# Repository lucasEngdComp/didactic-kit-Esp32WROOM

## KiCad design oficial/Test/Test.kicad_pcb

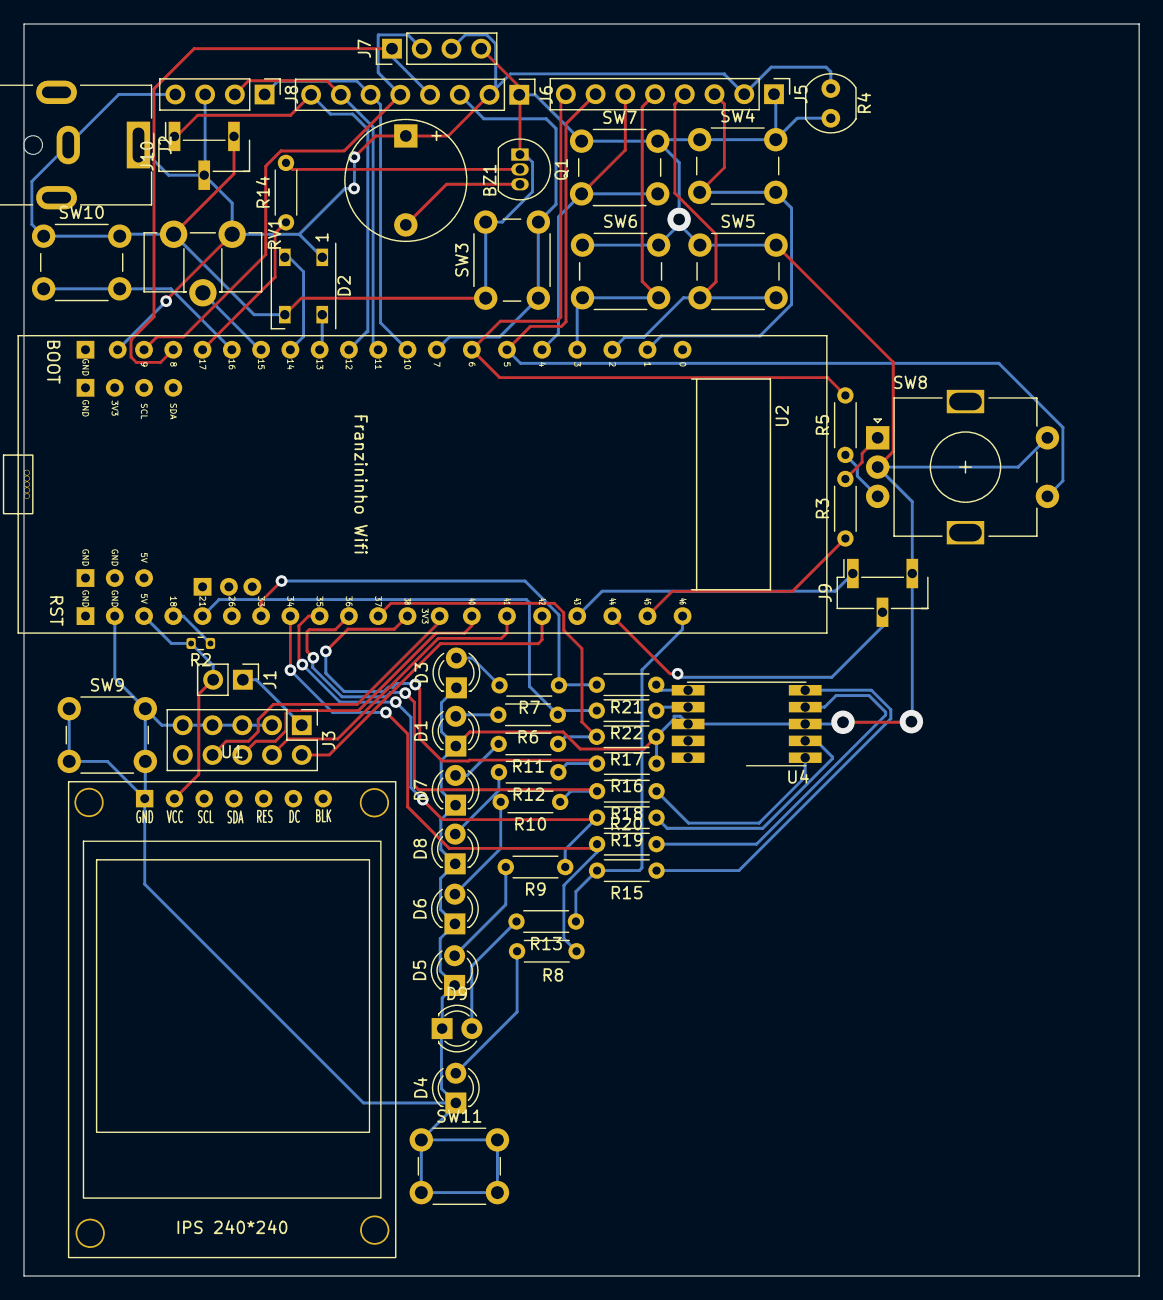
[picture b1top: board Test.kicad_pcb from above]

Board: 2 copper layers, 95.2 x 106.9 mm, 54 parts (0 on the bottom side), 54 nets.

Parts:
BZ1: Buzzer; Buzzer_12x9.5RM7.6
D1, D3, D4, D5, D6, D7, D8, D9: SFH4356P; LED_D3.0mm_IRBlack
D2: WS2812B; LED_WS2812B_PLCC4_5.0x5.0mm_P3.2mm
J1: Conn_01x02; PinHeader_1x02_P2.54mm_Vertical
J2: Jack-DC; BarrelJack_CUI_PJ-063AH_Horizontal
J3: Conn_02x05_Odd_Even; PinHeader_2x05_P2.54mm_Vertical
J5, J6: Conn_01x08_Male; PinHeader_1x08_P2.54mm_Vertical
J7, J8: Conn_01x04; PinHeader_1x04_P2.54mm_Vertical
J9, J10: Conn_01x03; PinHeader_1x03_P2.54mm_Vertical_SMD_Pin1Right
Q1: 2N3904; TO-92_Inline
R2: 10k; R_0603_1608Metric
R3, R5: 5K; R_Axial_DIN0204_L3.6mm_D1.6mm_P5.08mm_Horizontal
R4: VT93xx; R_LDR_4.9x4.2mm_P2.54mm_Vertical
R6, R7, R8, R9, R10, R11, R12, R13: 1K; R_Axial_DIN0204_L3.6mm_D1.6mm_P5.08mm_Horizontal
R14: 10K; R_Axial_DIN0204_L3.6mm_D1.6mm_P5.08mm_Horizontal
R15, R16, R17, R18, R19, R20, R21, R22: R; R_Axial_DIN0204_L3.6mm_D1.6mm_P5.08mm_Horizontal
RV1: R_Potentiometer_Trim; Potentiometer_ACP_CA9-H5_Horizontal
SW3, SW4, SW5, SW6, SW7, SW10: SW_Push; SW_PUSH_6mm
SW8: RotaryEncoder_Switch; RotaryEncoder_Alps_EC11E-Switch_Vertical_H20mm
SW9, SW11: SW_MEC_5G; SW_PUSH_6mm
U1: Display_240x240IPS; Display 240x240
U2: ESP32-S2-WROOM; FRANZININHO
U4: KCSC02-106

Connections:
GND: D1.1 (K), D2.3 (VSS), D3.1 (K), D4.1 (K), D5.1 (K), D6.1 (K), D7.1 (K), D8.1 (K), D9.1 (K), J2.2, J3.3, J3.5, J3.7, J3.9, J5.1, J6.1, J7.4, J8.4, J9.3, J10.3, Q1.1 (E), R4.2, R16.1, R17.1, RV1.3, SW3.1, SW4.1, SW5.1, SW6.1, SW7.1, SW8.C, SW8.S2, SW9.1 (A), SW9.2 (A), SW10.1, SW11.1 (A), SW11.2 (A), U2.GND, U4.3 (CC), U4.8 (CC)
GPIO1: J5.3, SW4.2, U2.1 (GND)
GPIO2: J5.4, SW5.2, U2.2 (3V3)
GPIO3: J5.5, SW6.2, U2.3 (GPIO0/BOOT)
GPIO4: J5.6, SW7.2, U2.4 (GPIO1/ADC1_CH0)
GPIO5: J5.7, SW8.S1, U2.5 (GPIO2/ADC1_CH1)
GPIO6: J5.8, R5.2, U2.6 (GPIO3/ADC1_CH2)
GPIO7: J6.3, SW3.2, U2.7 (GPIO4/ADC1_CH3)
GPIO8: J6.4, J7.1, U2.8 (GPIO5/ADC1_CH4)
GPIO9: J6.5, J7.2, U2.9 (GPIO6/ADC1_CH5)
GPIO10: J6.6, J8.1, U2.10 (GPIO7/ADC1_CH6)
GPIO11: J6.7, J8.2, U2.11 (GPIO8/ADC1_CH7)
GPIO12: J6.8, J10.1, U2.12 (GPIO9/ADC1_CH8)
GPIO13: D2.4 (DIN), U2.13 (GPIO10/ADC1_CH9)
GPIO14: D2.2 (DOUT), U2.14 (GPIO11/ADC2_CH0)
GPIO15: RV1.2, U2.15 (GPIO12/ADC2_CH1)
GPIO16: SW10.2, U2.16 (GPIO13/ADC2_CH2)
GPIO17: R14.1, U2.17 (GPIO14/ADC2_CH3)
GPIO18: R2.1, U2.18 (GPIO15/ADC2_CH4/XTAL_32K_P)
GPIO21: R6.1, R22.2, U2.21 (ADC2_CH6/DAC_1/GPIO18)
GPIO33: R7.1, R21.2, U2.33 (MTCK/JTAG/GPIO39)
GPIO34: R8.1, R20.2, U2.34 (MTDO/JTAG/GPIO40)
GPIO35: R9.1, R19.2, U2.35 (MTDI/JTAG/GPIO41)
GPIO36: R10.1, R18.2, U2.36 (MTMS/JTAG/GPIO42)
GPIO37: R11.1, R17.2, U2.37 (GPIO43/U0TXD/PROG)
GPIO38: R12.1, R16.2, U2.38 (GPIO44/U0RXD/PROG)
GPIO39: J3.8, U2.39
GPIO40: J3.6, U2.40 (GPIO46)
GPIO41: J3.4, U2.41 (CHIP/PU/RESET)
GPIO42: J3.2, U2.42 (GND)
GPIO43: J9.1, U2.43 (GND)
GPIO44: J9.2, U2.44
GPIO45: R3.1, U2.45
GPIO46: R13.1, R15.2, U2.46
unnamed: BZ1.2 (+), Q1.3 (C)
unnamed: D1.2 (A), R6.2
unnamed: D3.2 (A), R7.2
unnamed: D4.2 (A), R8.2
unnamed: D5.2 (A), R9.2
unnamed: D6.2 (A), R10.2
unnamed: D7.2 (A), R11.2
unnamed: D8.2 (A), R12.2
unnamed: D9.2 (A), R13.2
unnamed: J1.1, J3.1
unnamed: Q1.2 (B), R14.2
unnamed: R3.2, SW8.A
unnamed: R5.1, SW8.B
unnamed: R15.1, U4.5 (DP)
unnamed: R18.1, U4.1 (E)
unnamed: R19.1, U4.2 (D)
unnamed: R20.1, U4.4 (C)
unnamed: R21.1, U4.6 (B)
unnamed: R22.1, U4.7 (A)
VCC: BZ1.1 (-), D2.1 (VDD), J1.2, J2.1, J5.2, J6.2, J7.3, J8.3, J10.2, R2.2, R4.1, RV1.1, U2.3V3 (GPIO45), U2.5V (GPIO14/ADC2_CH3)

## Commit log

2022-05-24 files
